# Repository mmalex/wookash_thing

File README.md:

from a livestream with wookash on Friday 2026-01-16

(youtube link forthcoming)

small Raspberry Pi RP2040 'demo' project, with 4 choc-switch buttons, rgb leds, a TFT screen, captouch around the bezel, an SWD programming header, lipo battery connection, and speaker connections.

Mostly untested - planning to order shortly to see if it works.

See [notes.txt](notes.txt) for JLC part numbers used during the stream, and a few links.

* keyboard lib - https://github.com/ebastler/marbastlib
* easyeda2kicad - https://github.com/uPesy/easyeda2kicad.py
* jlc part search - https://yaqwsx.github.io/jlcparts/#/
* keyswitch 3d models https://github.com/koktoh/keyswitch_model.git

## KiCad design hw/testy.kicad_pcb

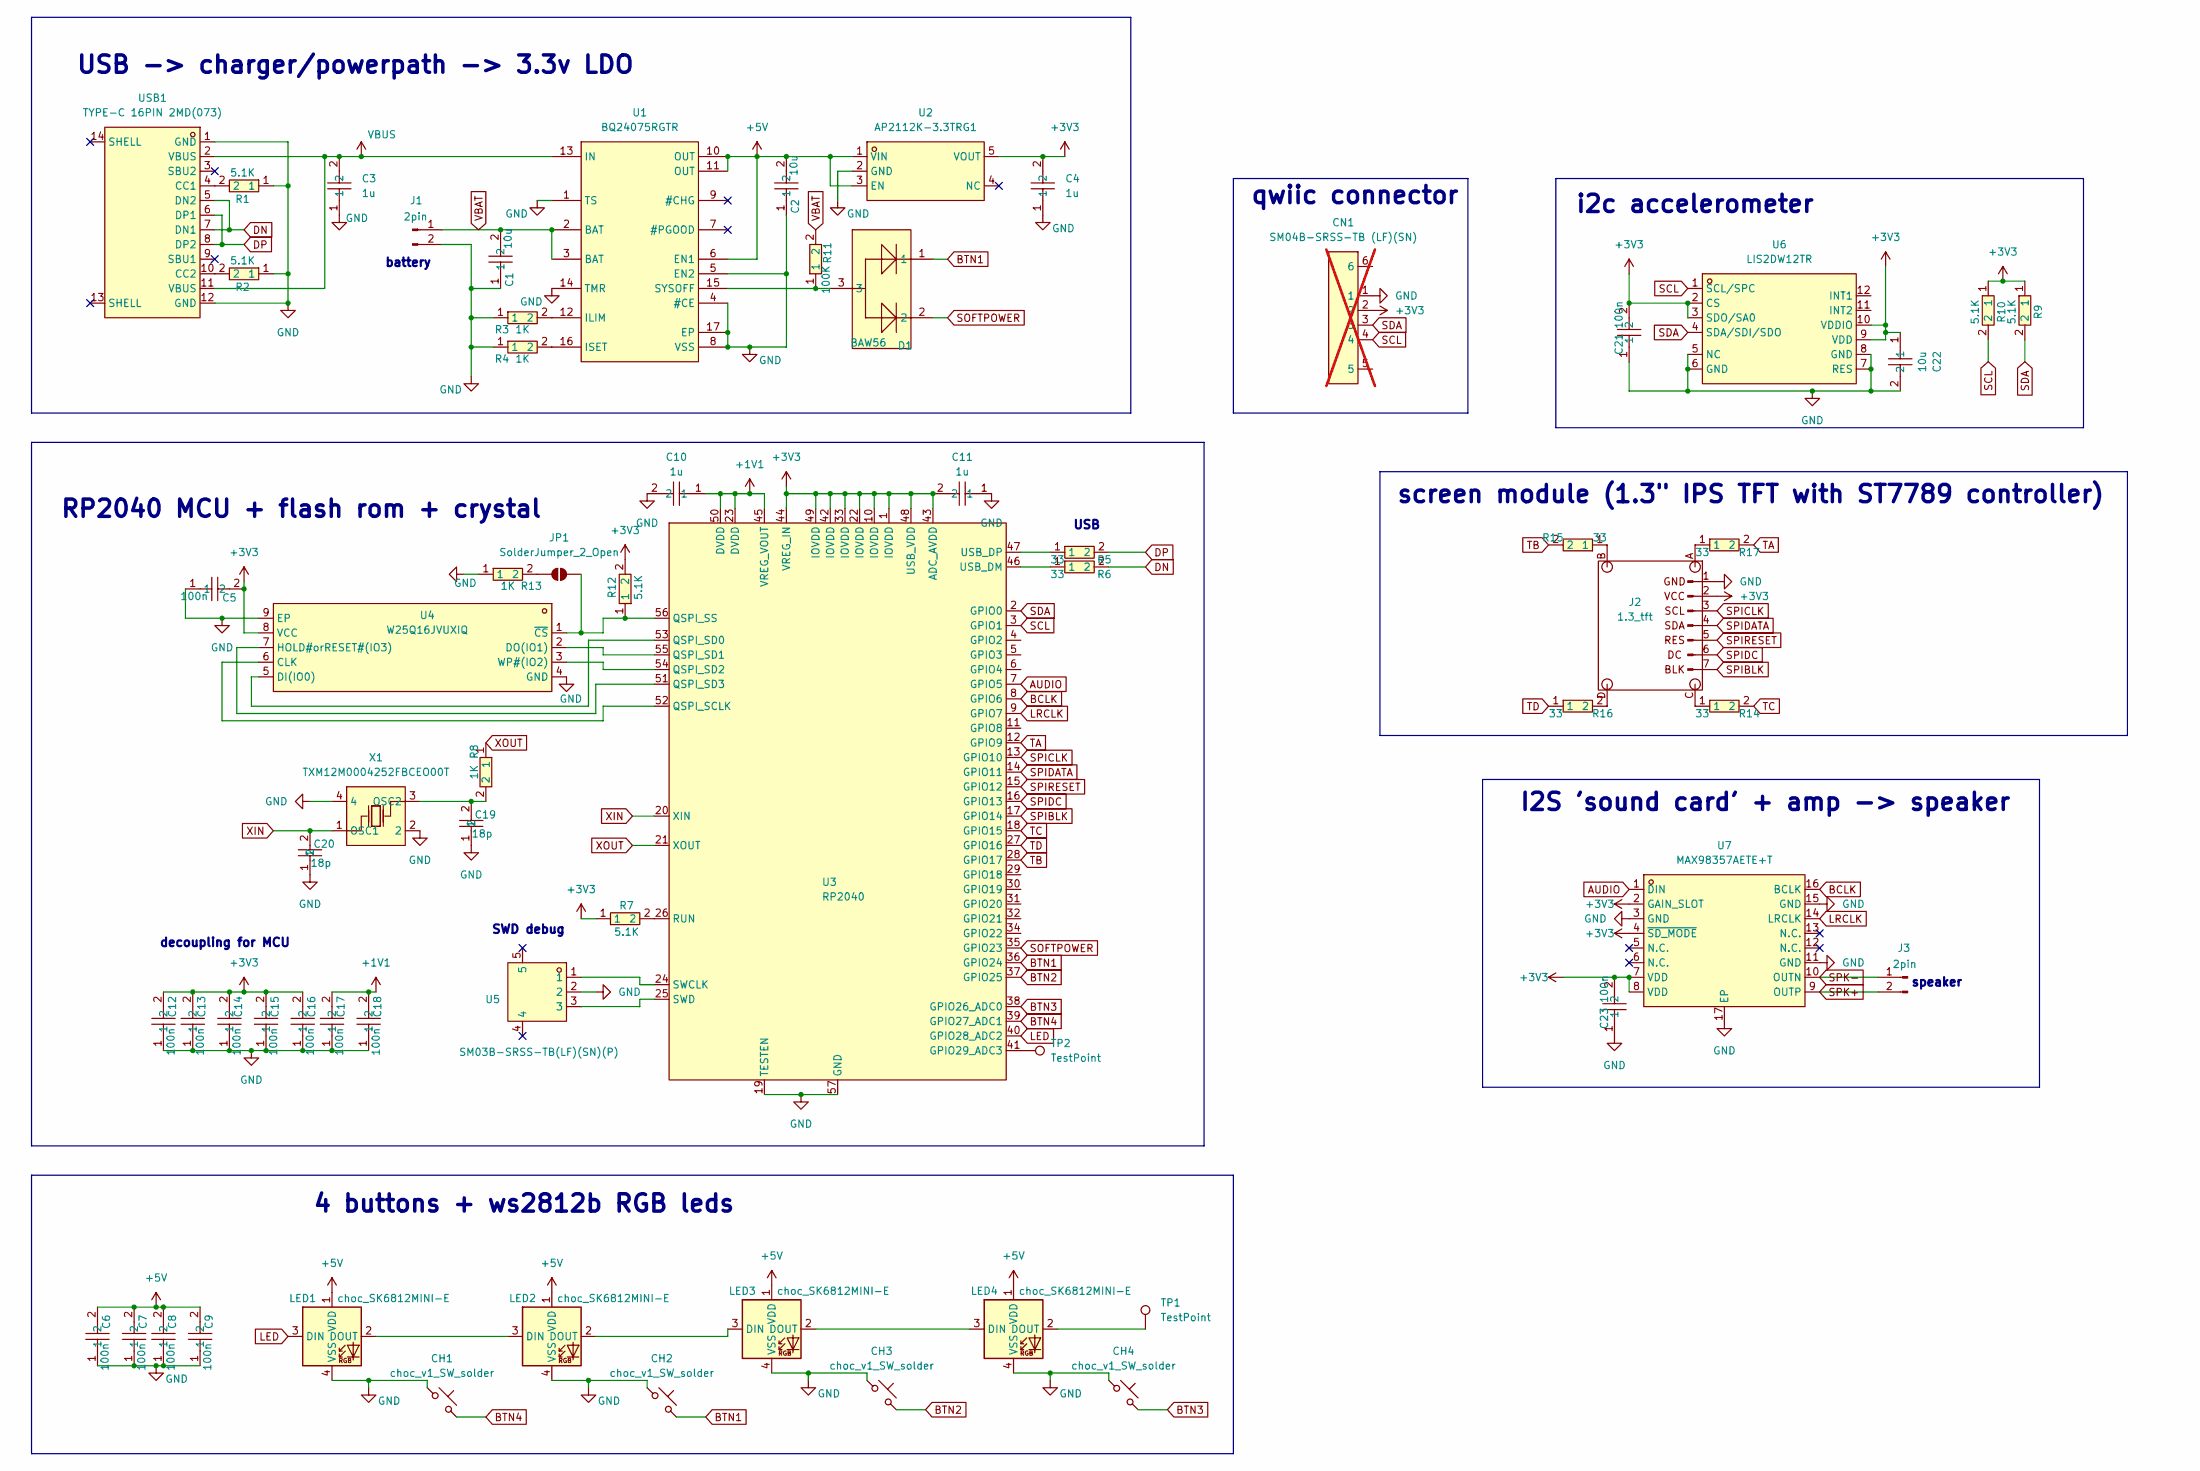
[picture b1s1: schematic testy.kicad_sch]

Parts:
C1, C2, C22: 10u; C0805; LCSC Part C15850
C3, C4, C10, C11: 1u; C0402; LCSC Part C52923
C5, C6, C7, C8, C9, C12, C13, C14, C15, C16, C17, C18, C21, C23: 100n; C0402; LCSC Part C307331
C19, C20: 18p; C0402; LCSC Part C1549
CH1, CH2, CH3, CH4: choc_v1_SW_solder; SW_choc_v1_1u
CN1: SM04B-SRSS-TB (LF)(SN); CONN-SMD_4P-P1.00_SM04B-SRSS-TB-LF-SN; LCSC Part C160404; not fitted
D1: BAW56; SOT-23-3_L2.9-W1.3-P1.90-LS2.4-BL-1; LCSC Part C7502729
J1, J3: 2pin; PinHeader_1x02_P2.54mm_Vertical
J2: 1.3_tft; tft 1.3
JP1: SolderJumper_2_Open; SolderJumper-2_P1.3mm_Open_RoundedPad1.0x1.5mm
LED1, LED2, LED3, LED4: choc_SK6812MINI-E; LED_choc_6028R; LCSC C5149201
R1, R2, R7, R9, R10, R12: 5.1K; R0402; LCSC Part C25905
R3, R4, R8, R13: 1K; R0402; LCSC Part C11702
R5, R6, R14, R15, R16, R17: 33; R0402; LCSC Part C25105
R11: 100K; R0402; LCSC Part C25803
TP1, TP2: TestPoint; TestPoint_Pad_D1.0mm
U1: BQ24075RGTR; QFN-16_L3.0-W3.0-P0.50-TL-EP1.7; LCSC Part C15464
U2: AP2112K-3.3TRG1; SOT-25-5_L2.9-W1.6-P0.95-LS2.8-BL; LCSC Part C51118
U3: RP2040; LQFN-56_L7.0-W7.0-P0.4-EP; LCSC Part C2040
U4: W25Q16JVUXIQ; USON-8_L3.0-W2.0-P0.50-BL-EP; LCSC Part C2843335
U5: SM03B-SRSS-TB(LF)(SN)(P); CONN-SMD_SM03B-SRSS-TB-LF-SN-P; LCSC Part C160403
U6: LIS2DW12TR; LGA-12_L2.0-W2.0-P0.50-BL; LCSC Part C189624
U7: MAX98357AETE+T; TQFN-16_L3.0-W3.0-P0.50-BL-EP1.5; LCSC Part C910544
USB1: TYPE-C 16PIN 2MD(073); USB-C-SMD_TYPE-C-6PIN-2MD-073; LCSC Part C2765186
X1: TXM12M0004252FBCEO00T; OSC-SMD_4P-L2.5-W2.0-BL; LCSC Part C284155

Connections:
+1V1: C10.1, C17.2, C18.2, U3.23 (DVDD), U3.45 (VREG_VOUT), U3.50 (DVDD)
+3V3: C4.2, C5.2, C11.2, C12.2, C13.2, C14.2, C15.2, C16.2, C21.2, C22.1, C23.2, CN1.2, J2.2, R7.1, R9.1, R10.1, R12.2, U2.5 (VOUT), U3.1 (IOVDD), U3.10 (IOVDD), U3.22 (IOVDD), U3.33 (IOVDD), U3.42 (IOVDD), U3.43 (ADC_AVDD), U3.44 (VREG_IN), U3.48 (USB_VDD), U3.49 (IOVDD), U4.8 (VCC), U6.2 (CS), U6.3 (SDO/SA0), U6.9 (VDD), U6.10 (VDDIO), U7.2 (GAIN_SLOT), U7.4 (~SD_MODE), U7.7 (VDD), U7.8 (VDD)
+5V: C2.2, C6.2, C7.2, C8.2, C9.2, LED1.1 (VDD), LED2.1 (VDD), LED3.1 (VDD), LED4.1 (VDD), U1.6 (EN1), U1.10 (OUT), U1.11 (OUT), U2.1 (VIN), U2.3 (EN)
AUDIO: U3.7 (GPIO5), U7.1 (DIN)
BCLK: U3.8 (GPIO6), U7.16 (BCLK)
BTN1: CH2.2, D1.1, U3.36 (GPIO24)
BTN2: CH3.2, U3.37 (GPIO25)
BTN3: CH4.2, U3.38 (GPIO26_ADC0)
BTN4: CH1.2, U3.39 (GPIO27_ADC1)
DN: R6.2, USB1.5 (DN2), USB1.7 (DN1)
DP: R5.2, USB1.6 (DP1), USB1.8 (DP2)
GND: C1.1, C2.1, C3.1, C4.1, C5.1, C6.1, C7.1, C8.1, C9.1, C10.2, C11.1, C12.1, C13.1, C14.1, C15.1, C16.1, C17.1, C18.1, C19.1, C20.1, C21.1, C22.2, C23.1, CH1.1, CH2.1, CH3.1, CH4.1, CN1.1, J1.2, J2.1, LED1.4 (VSS), LED2.4 (VSS), LED3.4 (VSS), LED4.4 (VSS), R1.1, R2.1, R3.1, R4.1, R13.1, U1.1 (TS), U1.4 (#CE), U1.5 (EN2), U1.8 (VSS), U1.14 (TMR), U1.17 (EP), U2.2 (GND), U3.19 (TESTEN), U3.57 (GND), U4.4 (GND), U4.9 (EP), U5.2, U6.5 (NC), U6.6 (GND), U6.7 (RES), U6.8 (GND), U7.3 (GND), U7.11 (GND), U7.15 (GND), U7.17 (EP), USB1.1 (GND), USB1.12 (GND), X1.2, X1.4
LED: LED1.3 (DIN), U3.40 (GPIO28_ADC2)
LRCLK: U3.9 (GPIO7), U7.14 (LRCLK)
unnamed: J2.A, R17.1
unnamed: J2.B, R15.1
unnamed: J2.C, R14.1
unnamed: J2.D, R16.2
unnamed: JP1.1 (A), R13.2
unnamed: JP1.2 (B), R12.1, U3.56 (QSPI_SS), U4.1 (~CS)
unnamed: LED1.2 (DOUT), LED2.3 (DIN)
unnamed: LED2.2 (DOUT), LED3.3 (DIN)
unnamed: LED3.2 (DOUT), LED4.3 (DIN)
unnamed: LED4.2 (DOUT), TP1.1
unnamed: R3.2, U1.12 (ILIM)
unnamed: R4.2, U1.16 (ISET)
unnamed: D1.3, R11.1, U1.15 (SYSOFF)
unnamed: TP2.1, U3.41 (GPIO29_ADC3)
unnamed: U3.52 (QSPI_SCLK), U4.6 (CLK)
unnamed: U3.53 (QSPI_SD0), U4.5 (DI(IO0))
unnamed: U3.55 (QSPI_SD1), U4.2 (DO(IO1))
unnamed: U3.54 (QSPI_SD2), U4.3 (WP#(IO2))
unnamed: U3.51 (QSPI_SD3), U4.7 (HOLD#orRESET#(IO3))
unnamed: R7.2, U3.26 (RUN)
unnamed: U3.24 (SWCLK), U5.1
unnamed: U3.25 (SWD), U5.3
unnamed: R6.1, U3.46 (USB_DM)
unnamed: R5.1, U3.47 (USB_DP)
unnamed: R1.2, USB1.4 (CC1)
unnamed: R2.2, USB1.10 (CC2)
unnamed: C19.2, R8.2, X1.3 (OSC2)
SCL: CN1.4, R10.2, U3.3 (GPIO1), U6.1 (SCL/SPC)
SDA: CN1.3, R9.2, U3.2 (GPIO0), U6.4 (SDA/SDI/SDO)
SOFTPOWER: D1.2, U3.35 (GPIO23)
SPIBLK: J2.7, U3.17 (GPIO14)
SPICLK: J2.3, U3.13 (GPIO10)
SPIDATA: J2.4, U3.14 (GPIO11)
SPIDC: J2.6, U3.16 (GPIO13)
SPIRESET: J2.5, U3.15 (GPIO12)
SPK+: J3.2, U7.9 (OUTP)
SPK-: J3.1, U7.10 (OUTN)
TA: R17.2, U3.12 (GPIO9)
TB: R15.2, U3.28 (GPIO17)
TC: R14.2, U3.18 (GPIO15)
TD: R16.1, U3.27 (GPIO16)
VBAT: C1.2, J1.1, R11.2, U1.2 (BAT), U1.3 (BAT)
VBUS: C3.2, U1.13 (IN), USB1.2 (VBUS), USB1.11 (VBUS)
XIN: C20.2, U3.20 (XIN), X1.1 (OSC1)
XOUT: R8.1, U3.21 (XOUT)

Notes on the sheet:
4 buttons + ws2812b RGB leds
i2c accelerometer
SWD debug
speaker
qwiic connector
RP2040 MCU + flash rom + crystal
USB -> charger/powerpath -> 3.3v LDO
USB
screen module (1.3" IPS TFT with ST7789 controller)
I2S 'sound card' + amp -> speaker
battery
decoupling for MCU

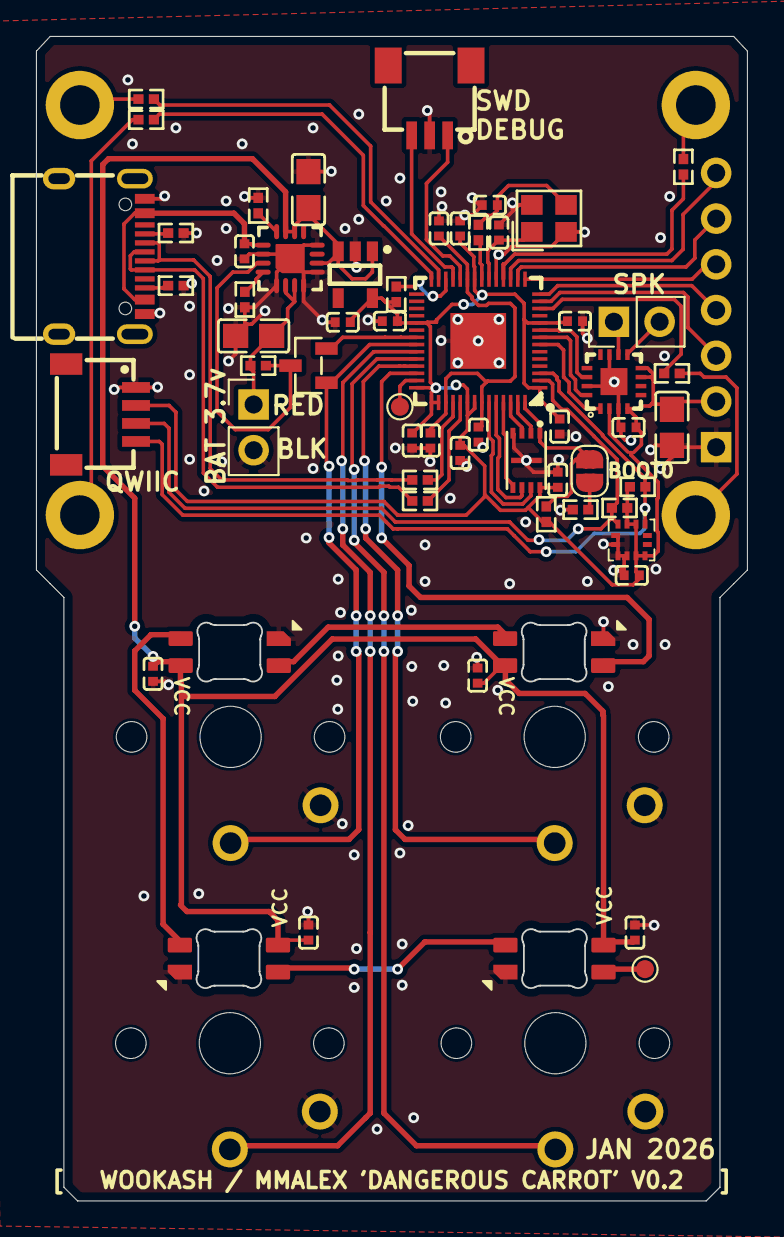
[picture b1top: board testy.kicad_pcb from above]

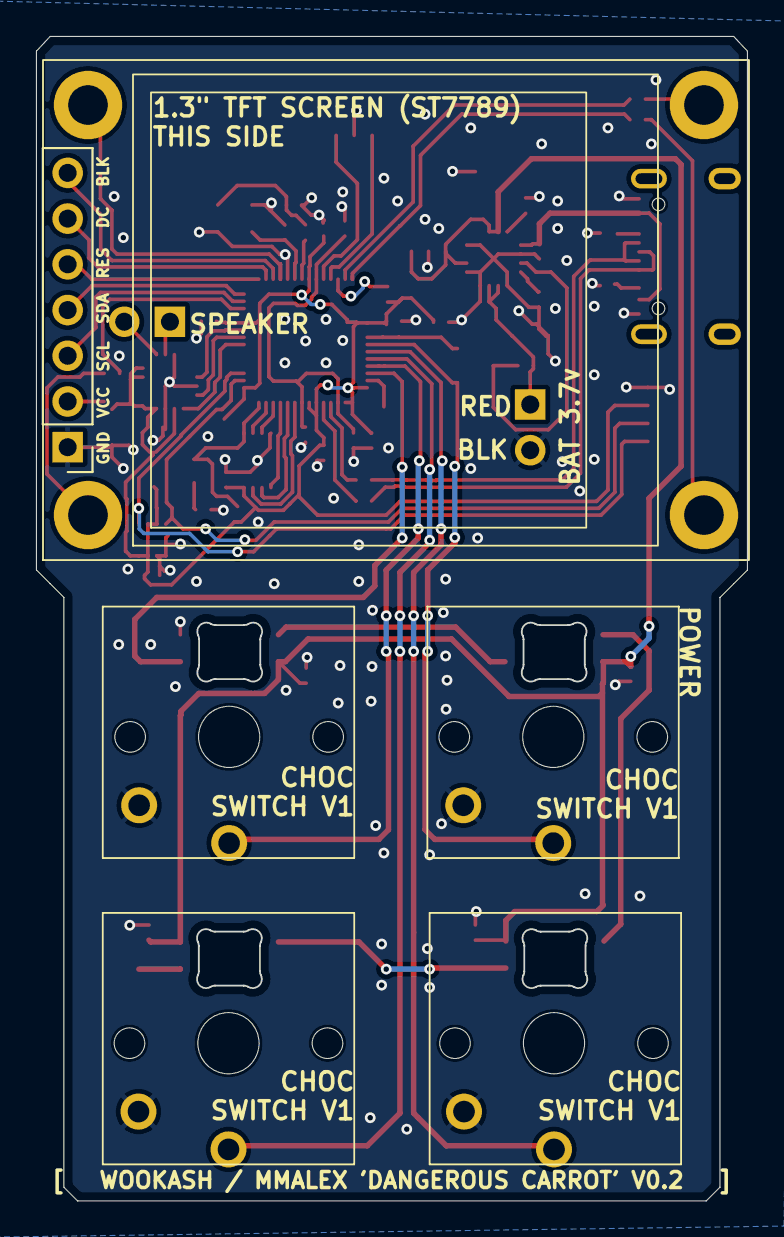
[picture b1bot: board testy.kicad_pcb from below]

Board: 2 copper layers, 39.4 x 64.6 mm, 65 parts (5 on the bottom side), 59 nets.

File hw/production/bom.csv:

Designator,Footprint,Quantity,Value,LCSC Part #
"C1, C2, C22",C0805,3,10u,C15850
"C10, C11, C3, C4",C0402,4,1u,C52923
"C12, C13, C14, C15, C16, C17, C18, C21, C23, C5, C6, C7, C8, C9",C0402,14,100n,C307331
"C19, C20",C0402,2,18p,C1549
"CH1, CH2, CH3, CH4",SW_choc_v1_1u,4,choc_v1_SW_solder,
D1,SOT-23-3_L2.9-W1.3-P1.90-LS2.4-BL-1,1,BAW56,C7502729
"J1, J3",PinHeader_1x02_P2.54mm_Vertical,2,2pin,
J2,tft 1.3,1,1.3_tft,
"LED1, LED2",LED_choc_6028R,2,choc_SK6812MINI-E,C5149201
"LED3, LED4",LED_choc_6028R-ROT,2,choc_SK6812MINI-E,C5149201
"R1, R10, R12, R2, R7, R9",R0402,6,5.1K,C25905
R11,R0402,1,1M,C26083
"R13, R3, R4, R8",R0402,4,1K,C11702
"R14, R15, R16, R17, R5, R6",R0402,6,33,C25105
"TP1, TP2",TestPoint_Pad_D1.0mm,2,TestPoint,
U1,QFN-16_L3.0-W3.0-P0.50-TL-EP1.7,1,BQ24075RGTR,C15464
U2,SOT-25-5_L2.9-W1.6-P0.95-LS2.8-BL,1,AP2112K-3.3TRG1,C51118
U3,LQFN-56_L7.0-W7.0-P0.4-EP,1,RP2040,C2040
U4,USON-8_L3.0-W2.0-P0.50-BL-EP,1,W25Q16JVUXIQ,C2843335
U5,CONN-SMD_SM03B-SRSS-TB-LF-SN-P,1,SM03B-SRSS-TB(LF)(SN)(P),C160403
U6,LGA-12_L2.0-W2.0-P0.50-BL,1,LIS2DW12TR,C189624
U7,TQFN-16_L3.0-W3.0-P0.50-BL-EP1.5,1,MAX98357AETE+T,C910544
USB1,USB-C-SMD_TYPE-C-6PIN-2MD-073,1,TYPE-C 16PIN 2MD(073),C2765186
X1,OSC-SMD_4P-L2.5-W2.0-BL,1,TXM12M0004252FBCEO00T,C284155

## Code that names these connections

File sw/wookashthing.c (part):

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#define ACCEL_I2C i2c0
#define ACCEL_ADDR 0x19 // 0011001b

#define SOFTPOWER_PIN 23
#define BUTTON_PINS 24
    // buttons are:
    // 3 0 aka 8 1
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  pio_sm_claim(AUDIO_PIO, 0);
  uint offset = pio_add_program(AUDIO_PIO, &audio_i2s_program);
  audio_i2s_program_init(AUDIO_PIO, 0, offset, AUDIO_PIN_DATA, AUDIO_PIN_BCLK);
  static_assert(AUDIO_PIN_BCLK < AUDIO_PIN_LRCLK, "BCLK must be less than LRCLK, otherwise use the swapped program");

  uint32_t system_clock_frequency = clock_get_hz(clk_sys);
  uint32_t sample_freq = 16000;
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static inline int maxi(int a, int b) { return a > b ? a : b; }

int main(void) {
  gpio_init(SOFTPOWER_PIN);
  gpio_set_dir(SOFTPOWER_PIN, GPIO_OUT);
  gpio_put(SOFTPOWER_PIN, 0); // 1=off, 0=on
  
  void stdio_rtt_init(void);
  stdio_rtt_init();
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    if (!(btns & BTN_BIT_TR)) tr_btn_not_down_time = now;
    if ((now - last_time_button_press) > 10*1000000 || (now - tr_btn_not_down_time) > 2*1000000) {
        // power down
        gpio_put(SOFTPOWER_PIN, 1);
        sleep_ms(100);
        // if we're still here, it means we must be on usb power...
    }
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
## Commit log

2026-01-18 first commit - added some silkscreen, pinswapped the buttons, added a fascia
2026-01-18 add 3d model of screen
2026-01-18 move 3d models
2026-01-18 update readme with pcs
2026-01-18 hw files as they were ordered at jlc
2026-01-28 bring up basic sw test
2026-02-15 change 1M pullup to 100k
2026-02-15 add updated prod files
